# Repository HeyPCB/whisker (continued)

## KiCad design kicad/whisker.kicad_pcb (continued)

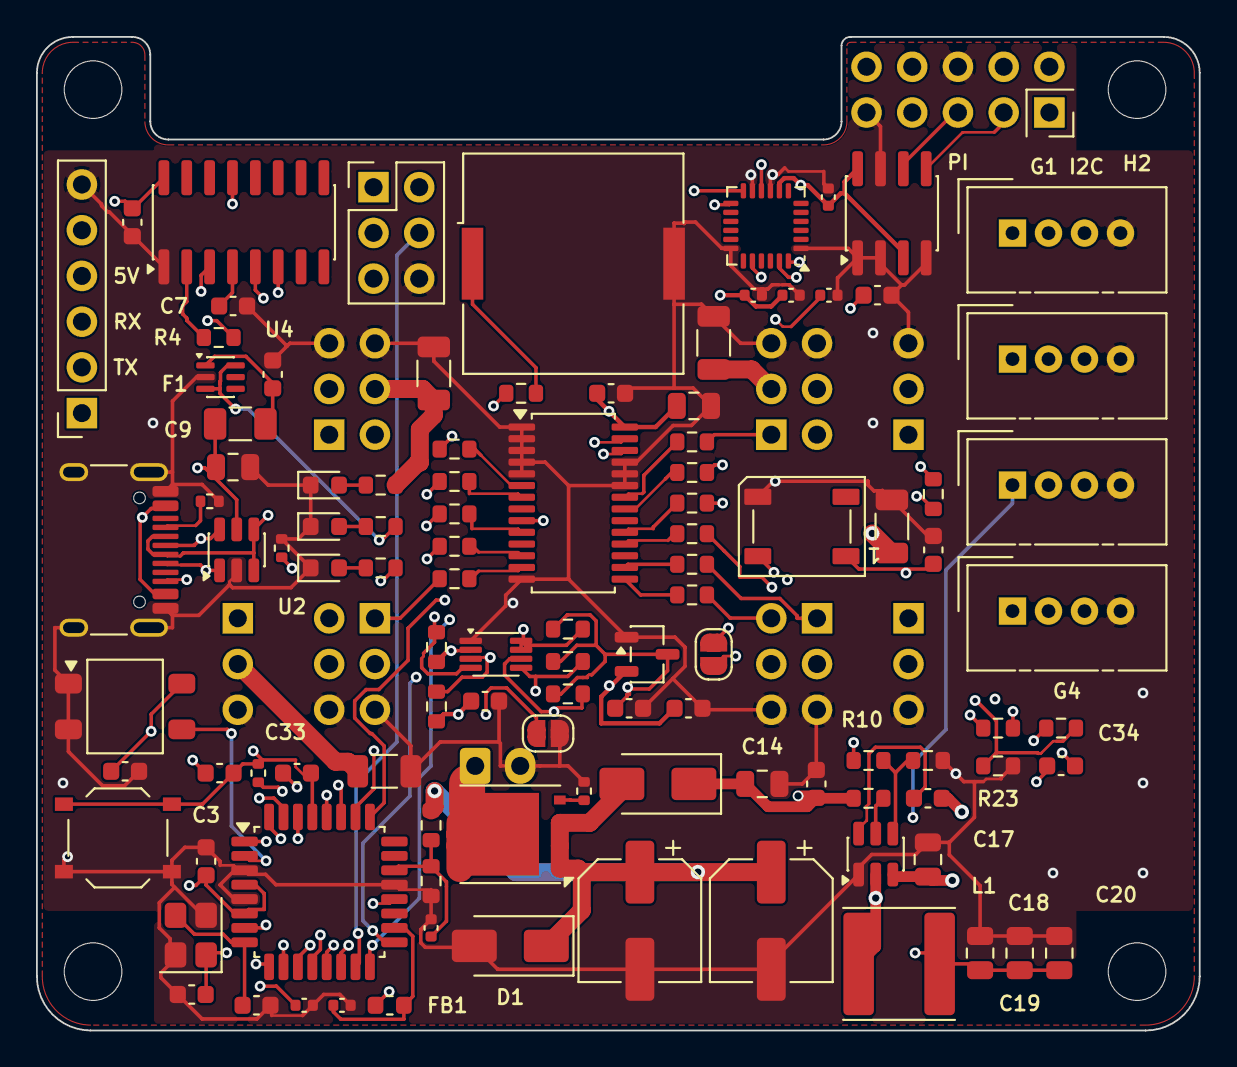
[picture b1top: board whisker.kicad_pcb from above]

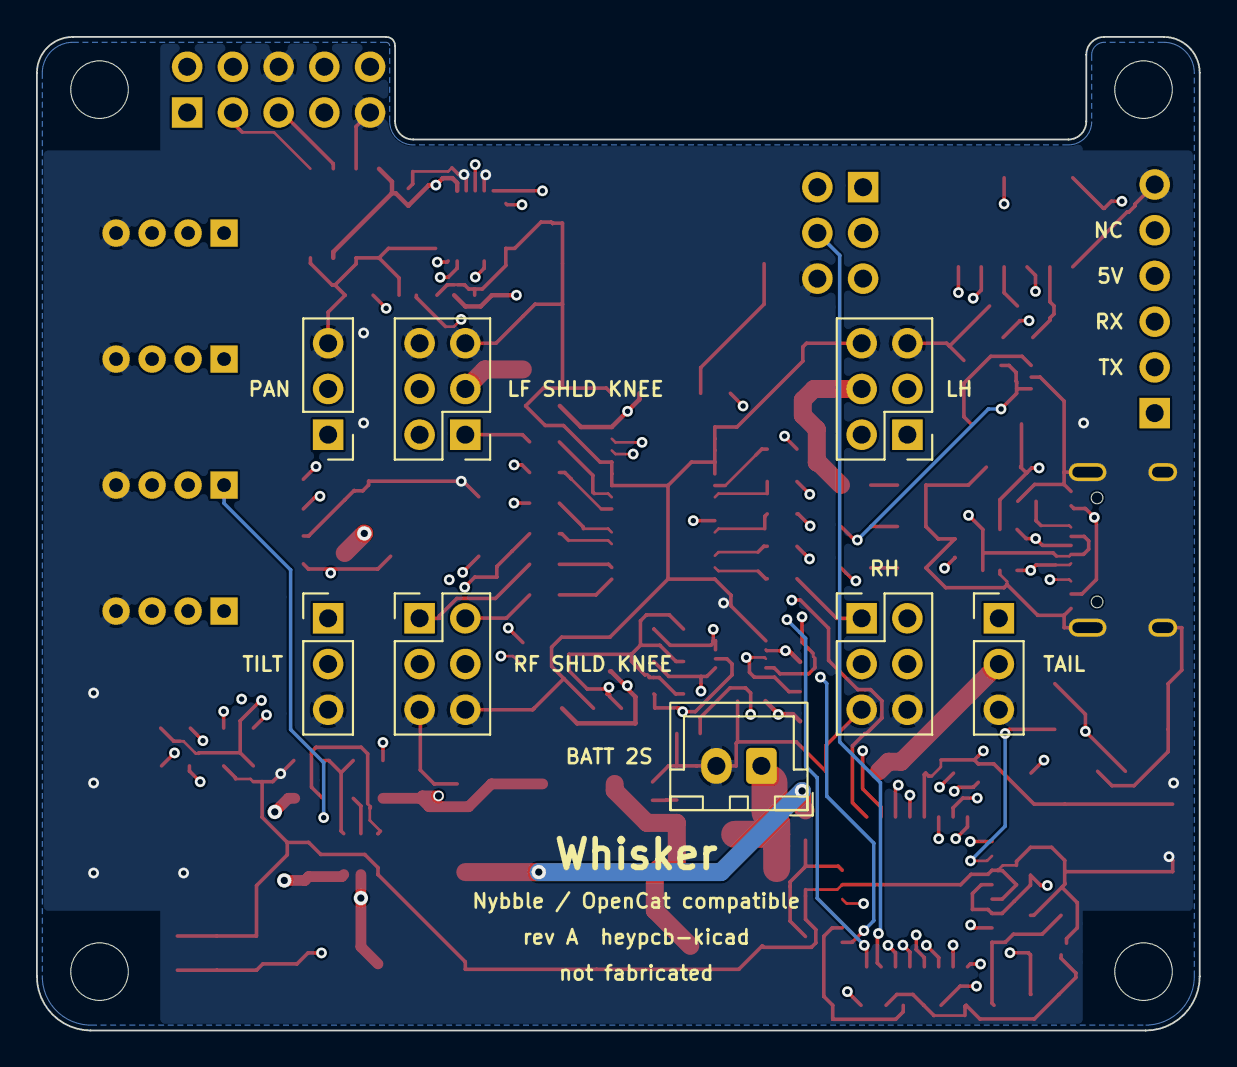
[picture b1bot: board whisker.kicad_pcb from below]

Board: 4 copper layers, 64.6 x 55.2 mm, 118 parts (8 on the bottom side), 81 nets.

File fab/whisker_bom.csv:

"Reference","Value","Footprint","MPN","LCSC","Qty"
"BZ1","PKLCS1212E4001","Buzzer_Beeper:Buzzer_Murata_PKLCS1212E","PKLCS1212E4001-R1","C113159","1"
"C1,C2","12pF","Capacitor_SMD:C_0603_1608Metric","CL10C120JB8NNNC","C38523","2"
"C3,C6,C7,C8,C16,C17,C23,C24,C31,C32,C33,C34","100nF","Capacitor_SMD:C_0603_1608Metric","CC0603KRX7R9BB104","C14663","12"
"C4,C5,C13,C26,C28,C30","100nF","Capacitor_SMD:C_0402_1005Metric","CL05B104KO5NNNC","C1525","6"
"C9,C25","10uF","Capacitor_SMD:C_0805_2012Metric","CL21A106KAYNNNE","C15850","2"
"C10,C21,C22","1uF","Capacitor_SMD:C_0603_1608Metric","CL10A105KB8NNNC","C15849","3"
"C11,C12","330uF 25V","Capacitor_SMD:CP_Elec_6.3x7.7","189RV0016","C7471878","2"
"C14,C15,C18,C19,C20","22uF","Capacitor_SMD:C_0805_2012Metric","CL21A226MAQNNNE","C45783","5"
"C27","10nF","Capacitor_SMD:C_0402_1005Metric","CL05B103KB5NNNC","C15195","1"
"C29","2.2nF","Capacitor_SMD:C_0603_1608Metric","0603B222K500NT","C1604","1"
"C35,C36,C37,C38","10uF","Capacitor_SMD:C_1206_3216Metric","CL31A106KBHNNNE","C13585","4"
"D1","SMAJ10A","Diode_SMD:D_SMA","SMAJ10A","C908764","1"
"D2","SS34","Diode_SMD:D_SMA","SS34","C8678","1"
"D3","Orange (BAT)","LED_SMD:LED_0603_1608Metric","XL-1608UOC-06","C965800","1"
"D4","WS2812B","LED_SMD:LED_WS2812B_PLCC4_5.0x5.0mm_P3.2mm","WS2812B-B/T","C2761795","1"
"D5","Green (D3)","LED_SMD:LED_0603_1608Metric","KT-0603G","C12624","1"
"D6","Blue (5V)","LED_SMD:LED_0603_1608Metric","NCD0603B1","C84266","1"
"F1","500mA","Fuse:Fuse_1206_3216Metric","1206L050/30NR","C7542947","1"
"FB1","120R@100MHz","Inductor_SMD:L_0603_1608Metric","BLM18PG121SN1D","C14709","1"
"J1","ICSP","Connector_PinHeader_2.54mm:PinHeader_2x03_P2.54mm_Vertical","PZ254V-12-6P","C492420","1"
"J2","USB-C","Connector_USB:USB_C_Receptacle_HRO_TYPE-C-31-M-12","TYPE-C-31-M-12","C165948","1"
"J3","BATT 2S","Connector_JST:JST_XH_B2B-XH-A_1x02_P2.50mm_Vertical","B2B-XH-A(LF)(SN)","C158012","1"
"J4,J5,J6,J7","GROVE","Connector:NS-Tech_Grove_1x04_P2mm_Vertical","ZX-HY2.0-4PZZ","C7429580","4"
"J8","SERIAL","Connector_PinSocket_2.54mm:PinSocket_1x06_P2.54mm_Vertical","2.54-1*6P母","C40877","1"
"J9","RPI 1-10","Connector_PinSocket_2.54mm:PinSocket_2x05_P2.54mm_Vertical","PM254V-12-10P-H85","C492399","1"
"J10,J14,J16","SERVO (3-row R/A)","Connector_PinHeader_2.54mm:PinHeader_1x03_P2.54mm_Vertical","PZ254-3-03-W-2.5-G0","C7429379","3"
"J11,J12,J13,J15","SERVO x2 (3-row R/A)","Connector_PinHeader_2.54mm:PinHeader_2x03_P2.54mm_Vertical","PZ254-3-03-W-2.5-G0","C7429379","4"
"L1","4.7uH","Inductor_SMD:L_Sunlord_SWPA6045S","SWPA6045S4R7MT","C78804","1"
"Q1","AON6411","Package_DFN_QFN:AO_DFN-8-1EP_5.55x5.2mm_P1.27mm_EP4.12x4.6mm","AON6411","C81007","1"
"R1,R5","10k","Resistor_SMD:R_0402_1005Metric","0402WGF1002TCE","C25744","2"
"R2,R3","5.1k","Resistor_SMD:R_0402_1005Metric","0402WGF5101TCE","C25905","2"
"R4,R19,R20,R21,R22,R24,R25,R26,R27,R28,R29,R30,R31,R32,R33,R34","1k","Resistor_SMD:R_0603_1608Metric","0603WAF1001T5E","C21190","16"
"R6","4.7k","Resistor_SMD:R_0603_1608Metric","0603WAF4701T5E","C23162","1"
"R7,R8","20k","Resistor_SMD:R_0603_1608Metric","0603WAF2002T5E","C4184","2"
"R9","82k","Resistor_SMD:R_0603_1608Metric","0603WAF8202T5E","C23254","1"
"R10","15k","Resistor_SMD:R_0603_1608Metric","0603WAF1502T5E","C22809","1"
"R11","100k","Resistor_SMD:R_0603_1608Metric","0603WAF1003T5E","C25803","1"
"R12","200k","Resistor_SMD:R_0603_1608Metric","0603WAF2003T5E","C25811","1"
"R13,R14,R15,R16","2.2k","Resistor_SMD:R_0603_1608Metric","0603WAF2201T5E","C4190","4"
"R17","100","Resistor_SMD:R_0603_1608Metric","0603WAF1000T5E","C22775","1"
"R18","330","Resistor_SMD:R_0603_1608Metric","0603WAF3300T5E","C23138","1"
"R23","2k","Resistor_SMD:R_0603_1608Metric","0603WAF2001T5E","C22975","1"
"SW1","RESET","Button_Switch_SMD:SW_Push_1P1T_XKB_TS-1187A","TS-1187A-B-A-B","C318884","1"
"U1","ATmega328P-AU","Package_QFP:TQFP-32_7x7mm_P0.8mm","ATMEGA328P-AU","C14877","1"
"U2","USBLC6-2SC6","Package_TO_SOT_SMD:SOT-23-6","USBLC6-2SC6","C7519","1"
"U3","CH340C","Package_SO:SOIC-16_3.9x9.9mm_P1.27mm","CH340C","C84681","1"
"U4","LM66100","Package_TO_SOT_SMD:SOT-363_SC-70-6","LM66100DCKR","C2869734","1"
"U5","TPS563201","Package_TO_SOT_SMD:SOT-23-6","TPS563201DDCR","C116592","1"
"U6","XC6206P332MR","Package_TO_SOT_SMD:SOT-23-3","XC6206P332MR-G","C5446","1"
"U7","PCA9306","Package_SO:VSSOP-8_2.3x2mm_P0.5mm","PCA9306DCUR","C33196","1"
"U8","PCA9685PW","Package_SO:TSSOP-28_4.4x9.7mm_P0.65mm","PCA9685PW,118","C2678753","1"
"U9","MPU-6050","Sensor_Motion:InvenSense_QFN-24_4x4mm_P0.5mm","MPU-6050","C24112","1"
"U10","AT24C64D","Package_SO:SOIC-8_3.9x4.9mm_P1.27mm","AT24C64D-SSHM-T","C6487","1"
"U11","IRM-H638T","OptoDevice:Everlight_IRM-H6xxT","IRM-H638T/TR2","C91447","1"
"Y1","16MHz","Crystal:Crystal_SMD_3225-4Pin_3.2x2.5mm","X322516MLB4SI","C13738","1"
